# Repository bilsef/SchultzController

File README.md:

# SchultzController

G-code controller for Siemens S (Schultz) feeders

## Arduino based controller in the hardware section.

The controller board distributes power to the feeders and provides the communication interface for 20 feeder units (40 lanes of components).  There are two versions of the controller board.  The KiCad files are in this folder.
* The 4 pin version has 20 individual 4 pin connectors.  One for each feeder unit.
* the 96 pin version has one 96 pin DIN connector compatible with the connector on the Siemens Communication Unit connector board.  This board is Siemens 1710470-Y1032-C1-01-86 and is inside of 00316265S05.
 
## Arduino code in the firmware section.

The board uses a Arduino Nano Every.  This is a low cost arduino which can easily be soldered to the control board.  Edit the config.h file in the arduino sketch to select the type of board you are using, then upload the sketch to the board.

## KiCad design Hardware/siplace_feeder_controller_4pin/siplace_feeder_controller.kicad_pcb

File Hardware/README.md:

# Have the board built by JLCPCB.com

* Go to jlcpcb.com and select SMT Assembly->Quote Now.
* Upload the zip file from the CAM directory of the board you want to build.
* Leave everything as default.  Scroll down to SMT Assembly and click Assemble your PCB boards.
* Choose Assemble bottom side.
* Choose your quantity and click Confirm.
* Upload the BOM and POS xlsx files from the CAM directory.
* Click NEXT.
* Confirm the BOM, click NEXT.
* Confirm the parts placement. If the placement doesn't show up, don't worry about it.  It has been verified.  Click SAVE TO CART and complete your purchase.
* [Buy me a coffee](https://www.buymeacoffee.com/cbVmnqB):coffee::smile:
* After you receive your boards, solder on the Arduino Nano Every using the surface mount pads and castellated holes.  Add connectors of your choice.  The 4 pin layout was made for JST B4B-XH-A(LF)(SN) connectors, but any 2.5mm compatible connector should work.

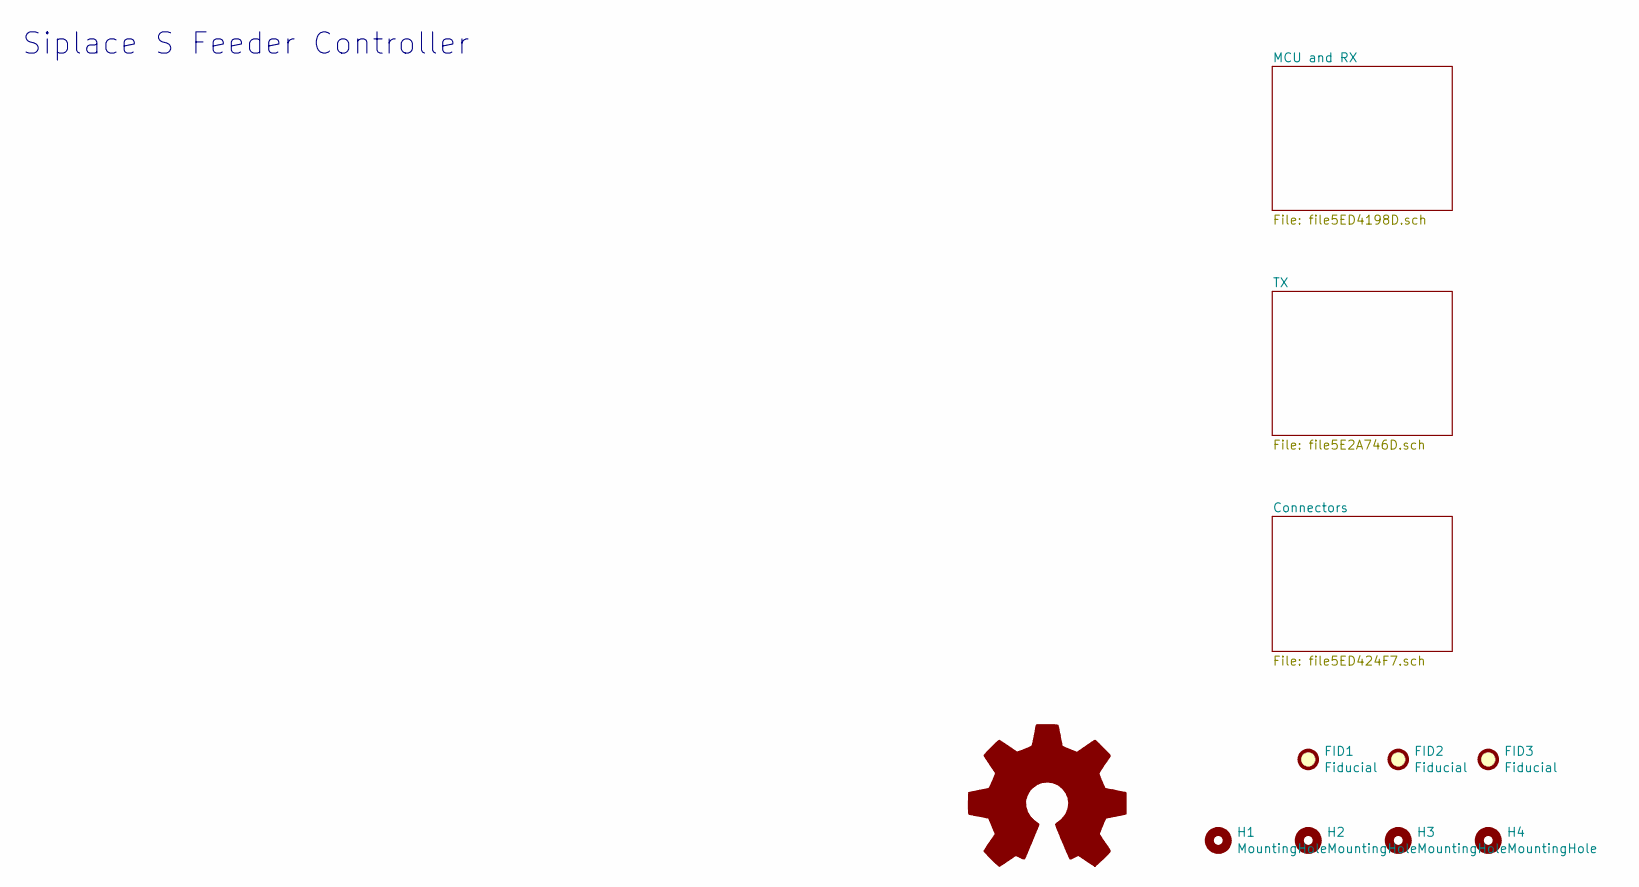
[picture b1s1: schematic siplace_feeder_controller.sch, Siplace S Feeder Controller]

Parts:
FID1, FID2, FID3: Fiducial; Fiducial_1mm_Mask3mm
H1, H2, H3, H4: MountingHole; MountingHole_3.2mm_M3

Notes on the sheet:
Siplace S Feeder Controller

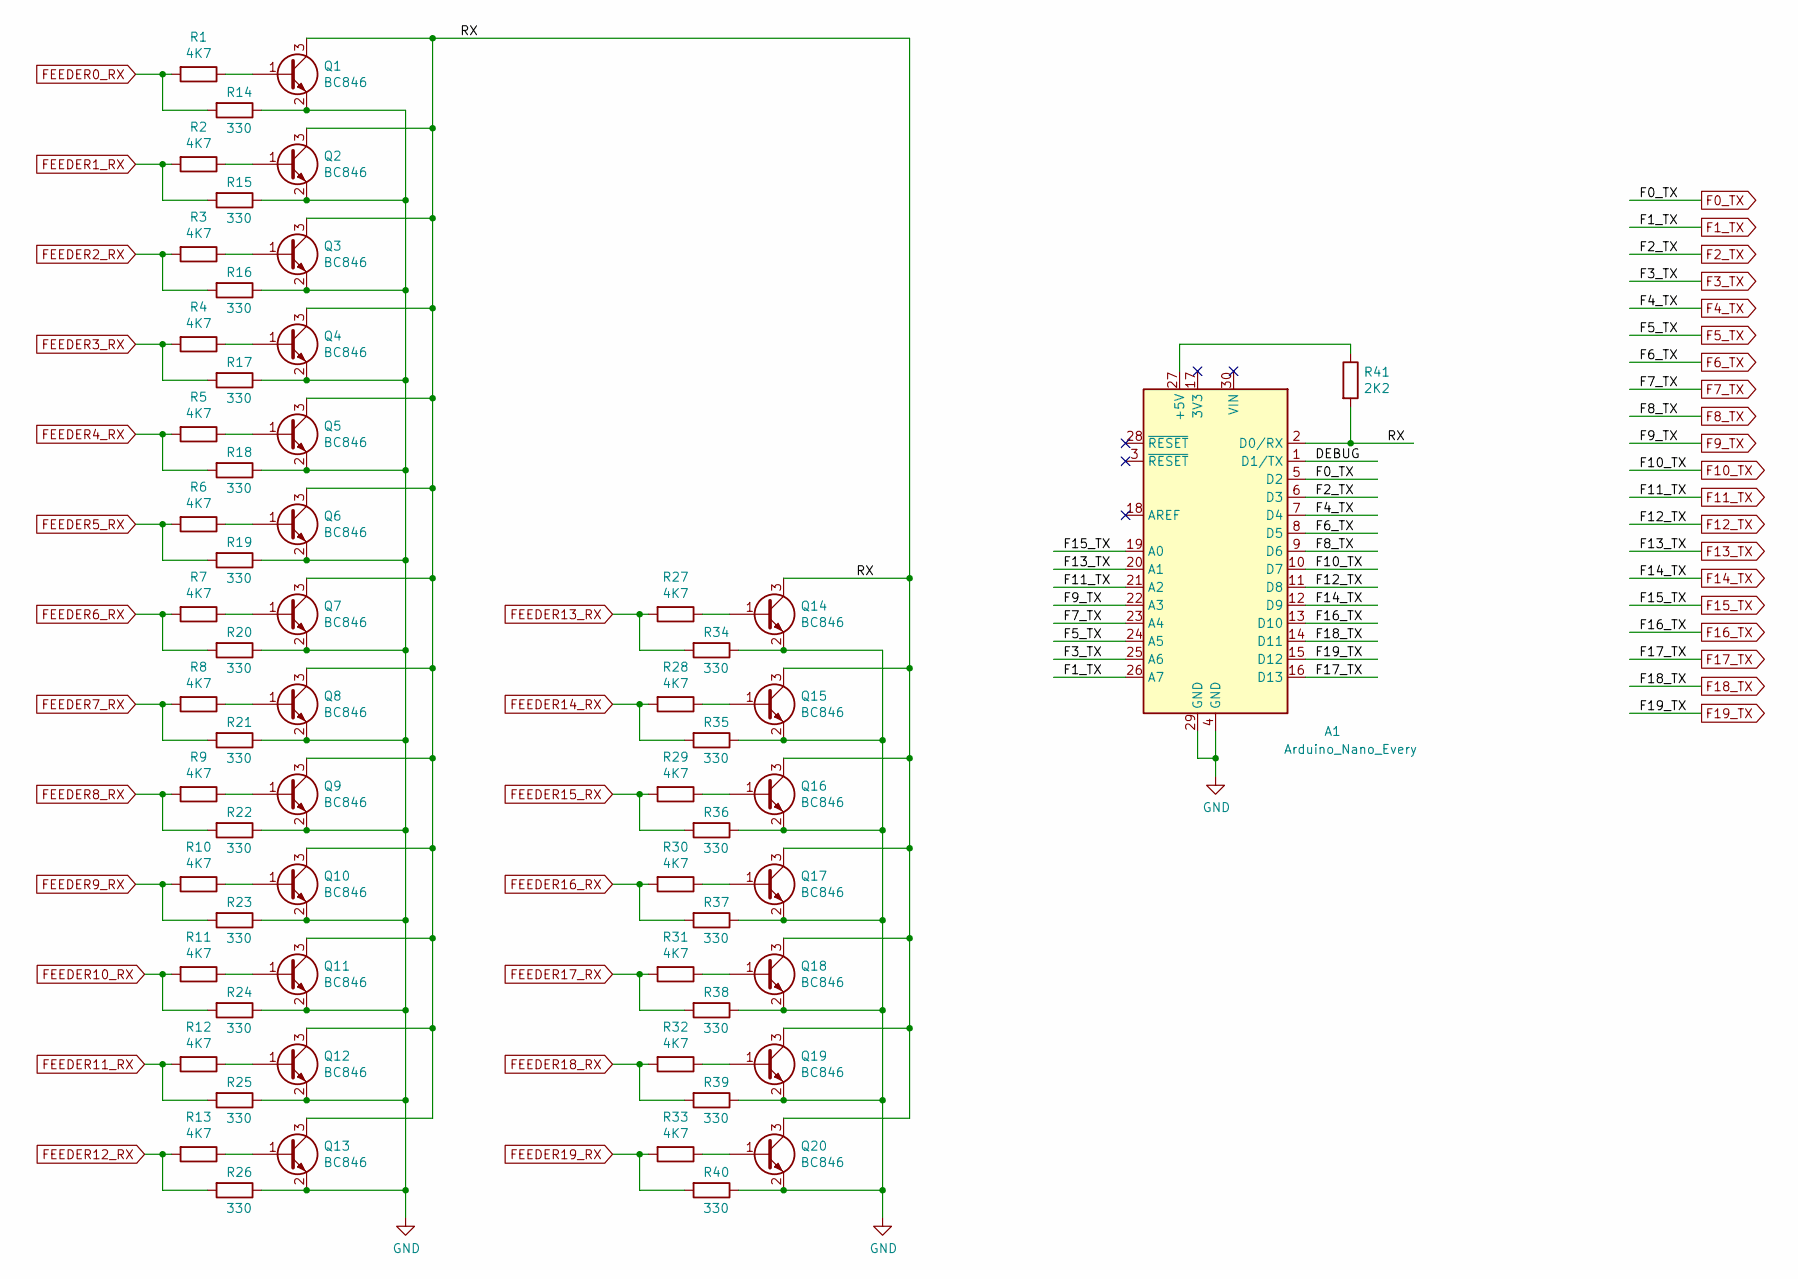
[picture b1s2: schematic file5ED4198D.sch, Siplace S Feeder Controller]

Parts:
A1: Arduino_Nano_Every; NANO_33_Footprint_SMD_Castell
Q1, Q2, Q3, Q4, Q5, Q6, Q7, Q8, Q9, Q10, Q11, Q12, Q13, Q14, Q15, Q16, Q17, Q18, Q19, Q20: BC846; SOT-23
R1, R2, R3, R4, R5, R6, R7, R8, R9, R10, R11, R12, R13, R27, R28, R29, R30, R31, R32, R33: 4K7; R_0603_1608Metric_Pad1.05x0.95mm_HandSolder
R14, R15, R16, R17, R18, R19, R20, R21, R22, R23, R24, R25, R26, R34, R35, R36, R37, R38, R39, R40: 330; R_0603_1608Metric_Pad1.05x0.95mm_HandSolder
R41: 2K2; R_0603_1608Metric_Pad1.05x0.95mm_HandSolder

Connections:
/MCU and RX/DEBUG: A1.1 (D1/TX)
/MCU and RX/RX: A1.2 (D0/RX), Q1.3 (C), Q2.3 (C), Q3.3 (C), Q4.3 (C), Q5.3 (C), Q6.3 (C), Q7.3 (C), Q8.3 (C), Q9.3 (C), Q10.3 (C), Q11.3 (C), Q12.3 (C), Q13.3 (C), Q14.3 (C), Q15.3 (C), Q16.3 (C), Q17.3 (C), Q18.3 (C), Q19.3 (C), Q20.3 (C), R41.2
F0_TX: A1.5 (D2); also elsewhere on the board
F1_TX: A1.26 (A7); also elsewhere on the board
F2_TX: A1.6 (D3); also elsewhere on the board
F3_TX: A1.25 (A6); also elsewhere on the board
F4_TX: A1.7 (D4); also elsewhere on the board
F5_TX: A1.24 (A5); also elsewhere on the board
F6_TX: A1.8 (D5); also elsewhere on the board
F7_TX: A1.23 (A4); also elsewhere on the board
F8_TX: A1.9 (D6); also elsewhere on the board
F9_TX: A1.22 (A3); also elsewhere on the board
F10_TX: A1.10 (D7); also elsewhere on the board
F11_TX: A1.21 (A2); also elsewhere on the board
F12_TX: A1.11 (D8); also elsewhere on the board
F13_TX: A1.20 (A1); also elsewhere on the board
F14_TX: A1.12 (D9); also elsewhere on the board
F15_TX: A1.19 (A0); also elsewhere on the board
F16_TX: A1.13 (D10); also elsewhere on the board
F17_TX: A1.16 (D13); also elsewhere on the board
F18_TX: A1.14 (D11); also elsewhere on the board
F19_TX: A1.15 (D12); also elsewhere on the board
FEEDER0_RX: R1.2, R14.2; also elsewhere on the board
FEEDER1_RX: R2.2, R15.2; also elsewhere on the board
FEEDER2_RX: R3.2, R16.2; also elsewhere on the board
FEEDER3_RX: R4.2, R17.2; also elsewhere on the board
FEEDER4_RX: R5.2, R18.2; also elsewhere on the board
FEEDER5_RX: R6.2, R19.2; also elsewhere on the board
FEEDER6_RX: R7.2, R20.2; also elsewhere on the board
FEEDER7_RX: R8.2, R21.2; also elsewhere on the board
FEEDER8_RX: R9.2, R22.2; also elsewhere on the board
FEEDER9_RX: R10.2, R23.2; also elsewhere on the board
FEEDER10_RX: R11.2, R24.2; also elsewhere on the board
FEEDER11_RX: R12.2, R25.2; also elsewhere on the board
FEEDER12_RX: R13.2, R26.2; also elsewhere on the board
FEEDER13_RX: R27.2, R34.2; also elsewhere on the board
FEEDER14_RX: R28.2, R35.2; also elsewhere on the board
FEEDER15_RX: R29.2, R36.2; also elsewhere on the board
FEEDER16_RX: R30.2, R37.2; also elsewhere on the board
FEEDER17_RX: R31.2, R38.2; also elsewhere on the board
FEEDER18_RX: R32.2, R39.2; also elsewhere on the board
FEEDER19_RX: R33.2, R40.2; also elsewhere on the board
GND: A1.4 (GND), A1.29 (GND), Q1.2 (E), Q2.2 (E), Q3.2 (E), Q4.2 (E), Q5.2 (E), Q6.2 (E), Q7.2 (E), Q8.2 (E), Q9.2 (E), Q10.2 (E), Q11.2 (E), Q12.2 (E), Q13.2 (E), Q14.2 (E), Q15.2 (E), Q16.2 (E), Q17.2 (E), Q18.2 (E), Q19.2 (E), Q20.2 (E), R14.1, R15.1, R16.1, R17.1, R18.1, R19.1, R20.1, R21.1, R22.1, R23.1, R24.1, R25.1, R26.1, R34.1, R35.1, R36.1, R37.1, R38.1, R39.1, R40.1; also elsewhere on the board
unnamed: A1.27 (+5V), R41.1
unnamed: Q1.1 (B), R1.1
unnamed: Q2.1 (B), R2.1
unnamed: Q3.1 (B), R3.1
unnamed: Q4.1 (B), R4.1
unnamed: Q5.1 (B), R5.1
unnamed: Q6.1 (B), R6.1
unnamed: Q7.1 (B), R7.1
unnamed: Q8.1 (B), R8.1
unnamed: Q9.1 (B), R9.1
unnamed: Q10.1 (B), R10.1
unnamed: Q11.1 (B), R11.1
unnamed: Q12.1 (B), R12.1
unnamed: Q13.1 (B), R13.1
unnamed: Q14.1 (B), R27.1
unnamed: Q15.1 (B), R28.1
unnamed: Q16.1 (B), R29.1
unnamed: Q17.1 (B), R30.1
unnamed: Q18.1 (B), R31.1
unnamed: Q19.1 (B), R32.1
unnamed: Q20.1 (B), R33.1

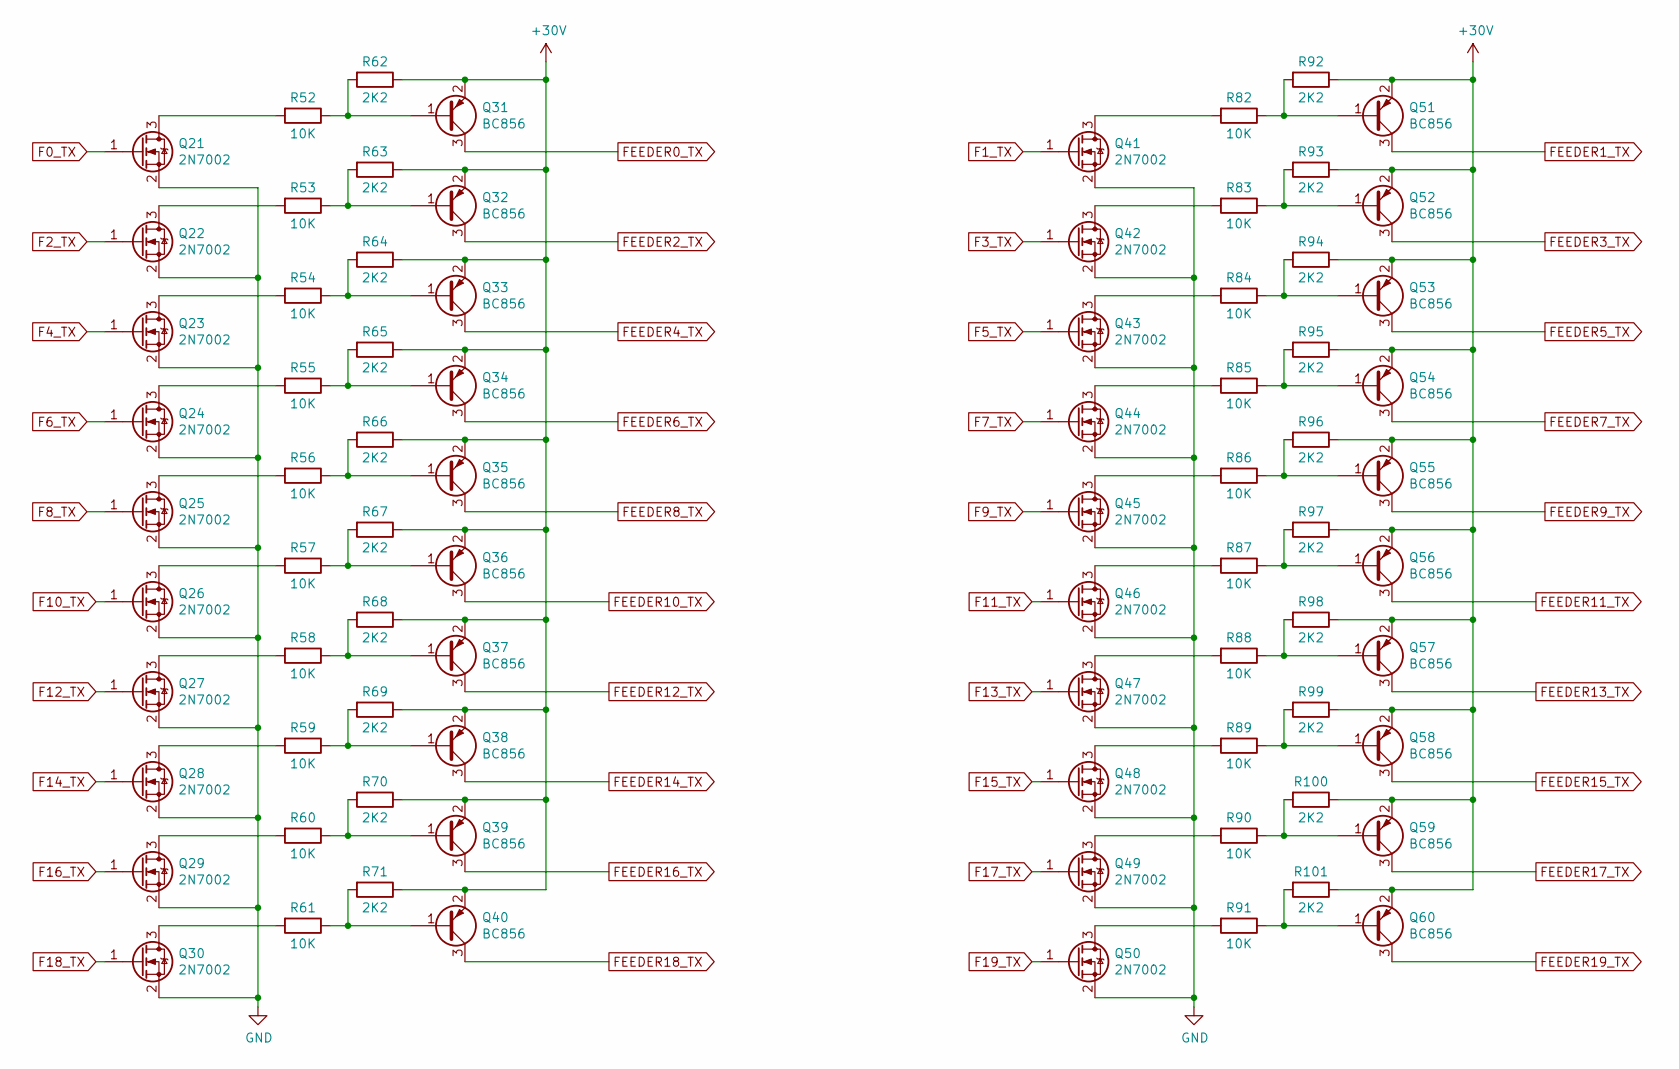
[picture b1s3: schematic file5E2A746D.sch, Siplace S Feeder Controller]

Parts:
Q21, Q22, Q23, Q24, Q25, Q26, Q27, Q28, Q29, Q30, Q41, Q42, Q43, Q44, Q45, Q46, Q47, Q48, Q49, Q50: 2N7002; SOT-23
Q31, Q32, Q33, Q34, Q35, Q36, Q37, Q38, Q39, Q40, Q51, Q52, Q53, Q54, Q55, Q56, Q57, Q58, Q59, Q60: BC856; SOT-23
R52, R53, R54, R55, R56, R57, R58, R59, R60, R61, R82, R83, R84, R85, R86, R87, R88, R89, R90, R91: 10K; R_0603_1608Metric_Pad1.05x0.95mm_HandSolder
R62, R63, R64, R65, R66, R67, R68, R69, R70, R71, R92, R93, R94, R95, R96, R97, R98, R99, R100, R101: 2K2; R_0603_1608Metric_Pad1.05x0.95mm_HandSolder

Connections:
+30V: Q31.2 (E), Q32.2 (E), Q33.2 (E), Q34.2 (E), Q35.2 (E), Q36.2 (E), Q37.2 (E), Q38.2 (E), Q39.2 (E), Q40.2 (E), Q51.2 (E), Q52.2 (E), Q53.2 (E), Q54.2 (E), Q55.2 (E), Q56.2 (E), Q57.2 (E), Q58.2 (E), Q59.2 (E), Q60.2 (E), R62.1, R63.1, R64.1, R65.1, R66.1, R67.1, R68.1, R69.1, R70.1, R71.1, R92.1, R93.1, R94.1, R95.1, R96.1, R97.1, R98.1, R99.1, R100.1, R101.1; also elsewhere on the board
F0_TX: Q21.1 (G); also elsewhere on the board
F1_TX: Q41.1 (G); also elsewhere on the board
F2_TX: Q22.1 (G); also elsewhere on the board
F3_TX: Q42.1 (G); also elsewhere on the board
F4_TX: Q23.1 (G); also elsewhere on the board
F5_TX: Q43.1 (G); also elsewhere on the board
F6_TX: Q24.1 (G); also elsewhere on the board
F7_TX: Q44.1 (G); also elsewhere on the board
F8_TX: Q25.1 (G); also elsewhere on the board
F9_TX: Q45.1 (G); also elsewhere on the board
F10_TX: Q26.1 (G); also elsewhere on the board
F11_TX: Q46.1 (G); also elsewhere on the board
F12_TX: Q27.1 (G); also elsewhere on the board
F13_TX: Q47.1 (G); also elsewhere on the board
F14_TX: Q28.1 (G); also elsewhere on the board
F15_TX: Q48.1 (G); also elsewhere on the board
F16_TX: Q29.1 (G); also elsewhere on the board
F17_TX: Q49.1 (G); also elsewhere on the board
F18_TX: Q30.1 (G); also elsewhere on the board
F19_TX: Q50.1 (G); also elsewhere on the board
FEEDER0_TX: Q31.3 (C); also elsewhere on the board
FEEDER1_TX: Q51.3 (C); also elsewhere on the board
FEEDER2_TX: Q32.3 (C); also elsewhere on the board
FEEDER3_TX: Q52.3 (C); also elsewhere on the board
FEEDER4_TX: Q33.3 (C); also elsewhere on the board
FEEDER5_TX: Q53.3 (C); also elsewhere on the board
FEEDER6_TX: Q34.3 (C); also elsewhere on the board
FEEDER7_TX: Q54.3 (C); also elsewhere on the board
FEEDER8_TX: Q35.3 (C); also elsewhere on the board
FEEDER9_TX: Q55.3 (C); also elsewhere on the board
FEEDER10_TX: Q36.3 (C); also elsewhere on the board
FEEDER11_TX: Q56.3 (C); also elsewhere on the board
FEEDER12_TX: Q37.3 (C); also elsewhere on the board
FEEDER13_TX: Q57.3 (C); also elsewhere on the board
FEEDER14_TX: Q38.3 (C); also elsewhere on the board
FEEDER15_TX: Q58.3 (C); also elsewhere on the board
FEEDER16_TX: Q39.3 (C); also elsewhere on the board
FEEDER17_TX: Q59.3 (C); also elsewhere on the board
FEEDER18_TX: Q40.3 (C); also elsewhere on the board
FEEDER19_TX: Q60.3 (C); also elsewhere on the board
GND: Q21.2 (S), Q22.2 (S), Q23.2 (S), Q24.2 (S), Q25.2 (S), Q26.2 (S), Q27.2 (S), Q28.2 (S), Q29.2 (S), Q30.2 (S), Q41.2 (S), Q42.2 (S), Q43.2 (S), Q44.2 (S), Q45.2 (S), Q46.2 (S), Q47.2 (S), Q48.2 (S), Q49.2 (S), Q50.2 (S); also elsewhere on the board
unnamed: Q21.3 (D), R52.2
unnamed: Q22.3 (D), R53.2
unnamed: Q23.3 (D), R54.2
unnamed: Q24.3 (D), R55.2
unnamed: Q25.3 (D), R56.2
unnamed: Q26.3 (D), R57.2
unnamed: Q27.3 (D), R58.2
unnamed: Q28.3 (D), R59.2
unnamed: Q29.3 (D), R60.2
unnamed: Q30.3 (D), R61.2
unnamed: Q31.1 (B), R52.1, R62.2
unnamed: Q32.1 (B), R53.1, R63.2
unnamed: Q33.1 (B), R54.1, R64.2
unnamed: Q34.1 (B), R55.1, R65.2
unnamed: Q35.1 (B), R56.1, R66.2
unnamed: Q36.1 (B), R57.1, R67.2
unnamed: Q37.1 (B), R58.1, R68.2
unnamed: Q38.1 (B), R59.1, R69.2
unnamed: Q39.1 (B), R60.1, R70.2
unnamed: Q40.1 (B), R61.1, R71.2
unnamed: Q41.3 (D), R82.2
unnamed: Q42.3 (D), R83.2
unnamed: Q43.3 (D), R84.2
unnamed: Q44.3 (D), R85.2
unnamed: Q45.3 (D), R86.2
unnamed: Q46.3 (D), R87.2
unnamed: Q47.3 (D), R88.2
unnamed: Q48.3 (D), R89.2
unnamed: Q49.3 (D), R90.2
unnamed: Q50.3 (D), R91.2
unnamed: Q51.1 (B), R82.1, R92.2
unnamed: Q52.1 (B), R83.1, R93.2
unnamed: Q53.1 (B), R84.1, R94.2
unnamed: Q54.1 (B), R85.1, R95.2
unnamed: Q55.1 (B), R86.1, R96.2
unnamed: Q56.1 (B), R87.1, R97.2
unnamed: Q57.1 (B), R88.1, R98.2
unnamed: Q58.1 (B), R89.1, R99.2
unnamed: Q59.1 (B), R90.1, R100.2
unnamed: Q60.1 (B), R91.1, R101.2

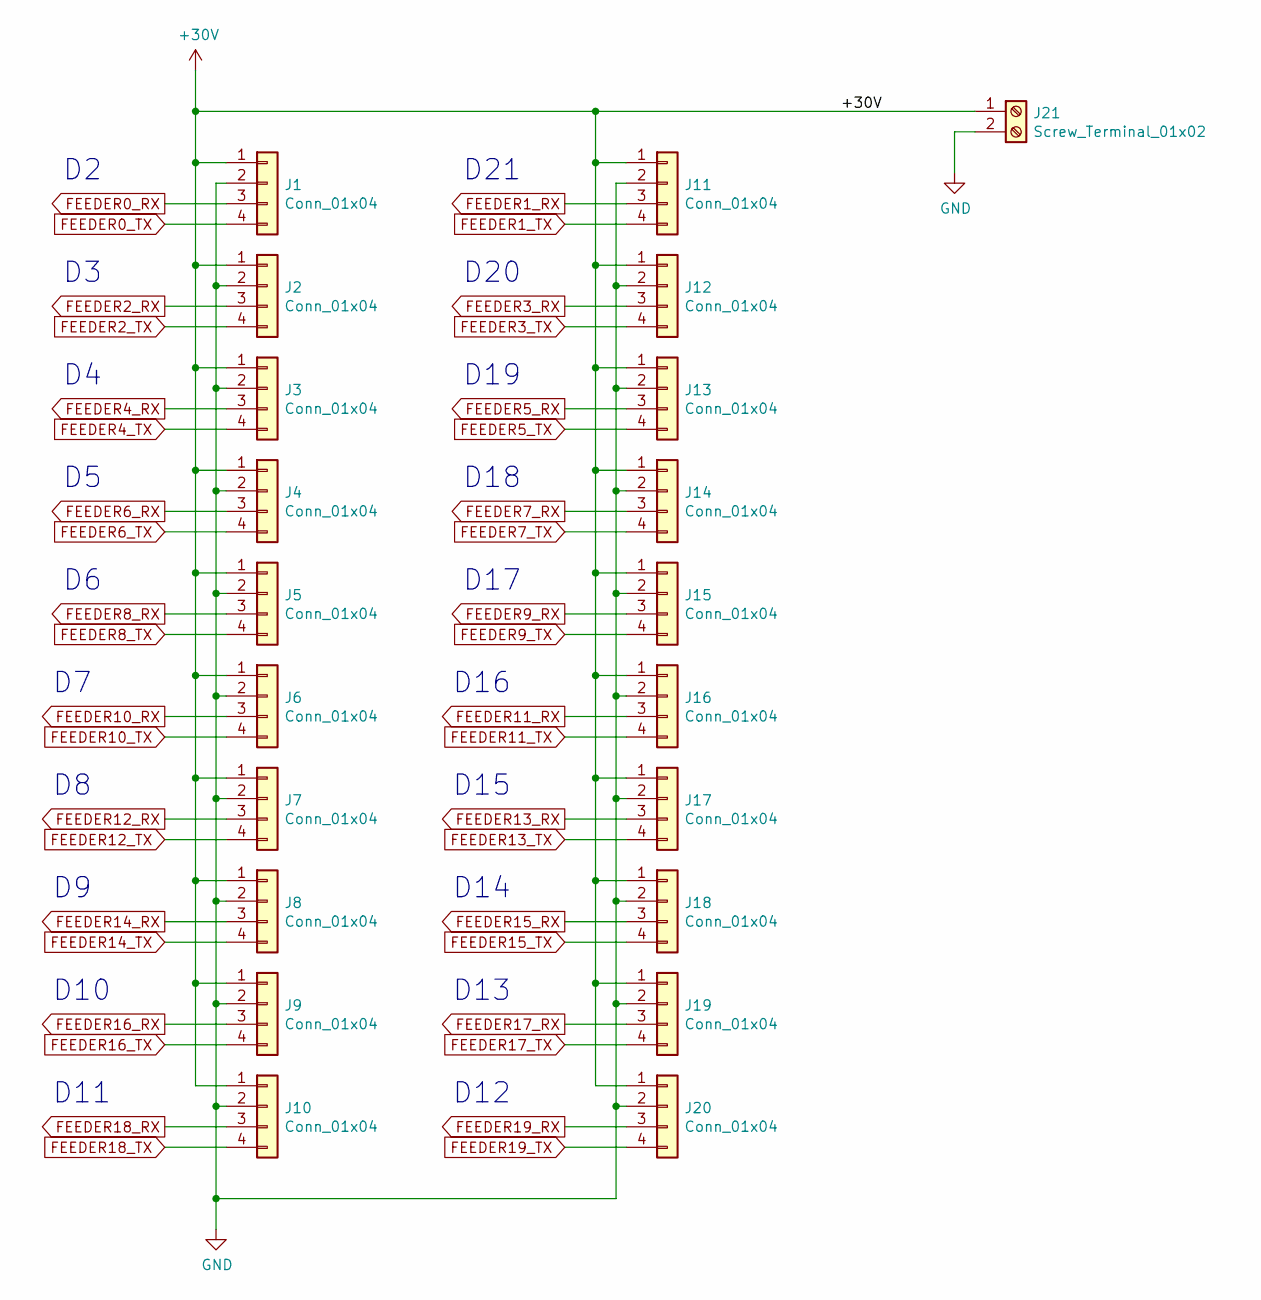
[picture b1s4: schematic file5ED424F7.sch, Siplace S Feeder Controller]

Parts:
J1, J2, J3, J4, J5, J6, J7, J8, J9, J10, J11, J12, J13, J14, J15, J16, J17, J18, J19, J20: Conn_01x04; JST_XH_B4B-XH-A_1x04_P2.50mm_Vertical
J21: Screw_Terminal_01x02; TerminalBlock_Phoenix_MKDS-1,5-2-5.08_1x02_P5.08mm_Horizont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

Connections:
+30V: J1.1, J2.1, J3.1, J4.1, J5.1, J6.1, J7.1, J8.1, J9.1, J10.1, J11.1, J12.1, J13.1, J14.1, J15.1, J16.1, J17.1, J18.1, J19.1, J20.1, J21.1; also elsewhere on the board
FEEDER0_RX: J1.3; also elsewhere on the board
FEEDER0_TX: J1.4; also elsewhere on the board
FEEDER1_RX: J11.3; also elsewhere on the board
FEEDER1_TX: J11.4; also elsewhere on the board
FEEDER2_RX: J2.3; also elsewhere on the board
FEEDER2_TX: J2.4; also elsewhere on the board
FEEDER3_RX: J12.3; also elsewhere on the board
FEEDER3_TX: J12.4; also elsewhere on the board
FEEDER4_RX: J3.3; also elsewhere on the board
FEEDER4_TX: J3.4; also elsewhere on the board
FEEDER5_RX: J13.3; also elsewhere on the board
FEEDER5_TX: J13.4; also elsewhere on the board
FEEDER6_RX: J4.3; also elsewhere on the board
FEEDER6_TX: J4.4; also elsewhere on the board
FEEDER7_RX: J14.3; also elsewhere on the board
FEEDER7_TX: J14.4; also elsewhere on the board
FEEDER8_RX: J5.3; also elsewhere on the board
FEEDER8_TX: J5.4; also elsewhere on the board
FEEDER9_RX: J15.3; also elsewhere on the board
FEEDER9_TX: J15.4; also elsewhere on the board
FEEDER10_RX: J6.3; also elsewhere on the board
FEEDER10_TX: J6.4; also elsewhere on the board
FEEDER11_RX: J16.3; also elsewhere on the board
FEEDER11_TX: J16.4; also elsewhere on the board
FEEDER12_RX: J7.3; also elsewhere on the board
FEEDER12_TX: J7.4; also elsewhere on the board
FEEDER13_RX: J17.3; also elsewhere on the board
FEEDER13_TX: J17.4; also elsewhere on the board
FEEDER14_RX: J8.3; also elsewhere on the board
FEEDER14_TX: J8.4; also elsewhere on the board
FEEDER15_RX: J18.3; also elsewhere on the board
FEEDER15_TX: J18.4; also elsewhere on the board
FEEDER16_RX: J9.3; also elsewhere on the board
FEEDER16_TX: J9.4; also elsewhere on the board
FEEDER17_RX: J19.3; also elsewhere on the board
FEEDER17_TX: J19.4; also elsewhere on the board
FEEDER18_RX: J10.3; also elsewhere on the board
FEEDER18_TX: J10.4; also elsewhere on the board
FEEDER19_RX: J20.3; also elsewhere on the board
FEEDER19_TX: J20.4; also elsewhere on the board
GND: J1.2, J2.2, J3.2, J4.2, J5.2, J6.2, J7.2, J8.2, J9.2, J10.2, J11.2, J12.2, J13.2, J14.2, J15.2, J16.2, J17.2, J18.2, J19.2, J20.2, J21.2; also elsewhere on the board

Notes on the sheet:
D21
D10
D11
D20
D19
D18
D17
D16
D15
D14
D13
D12

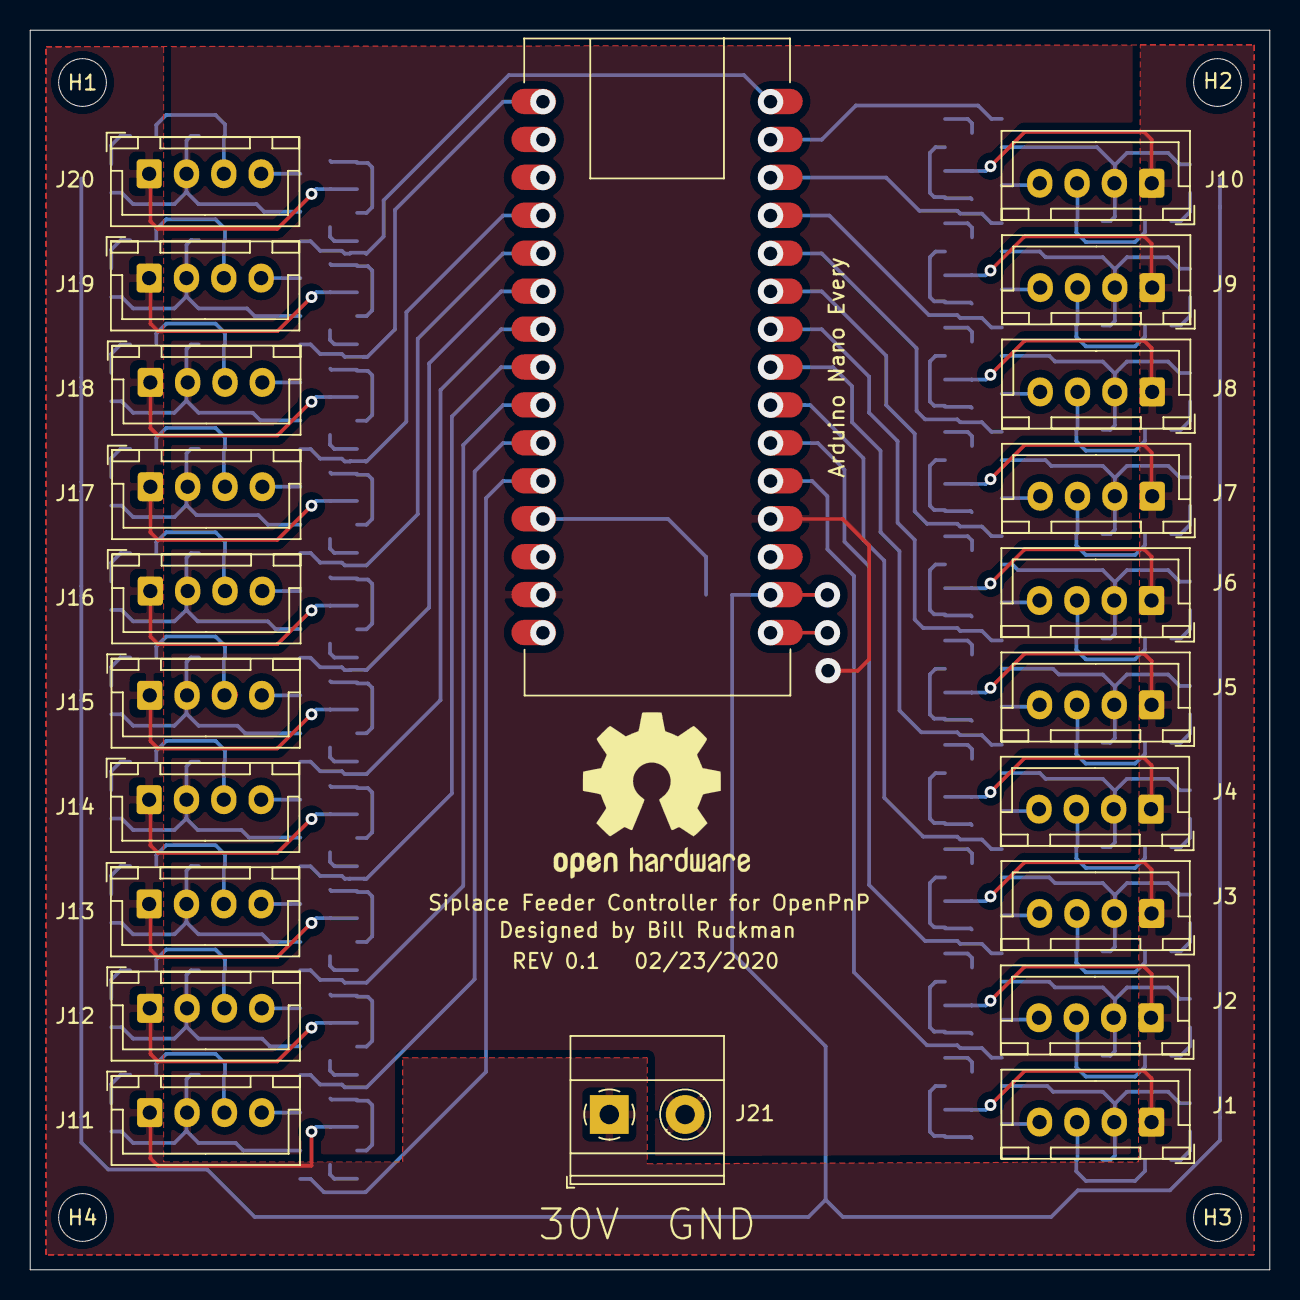
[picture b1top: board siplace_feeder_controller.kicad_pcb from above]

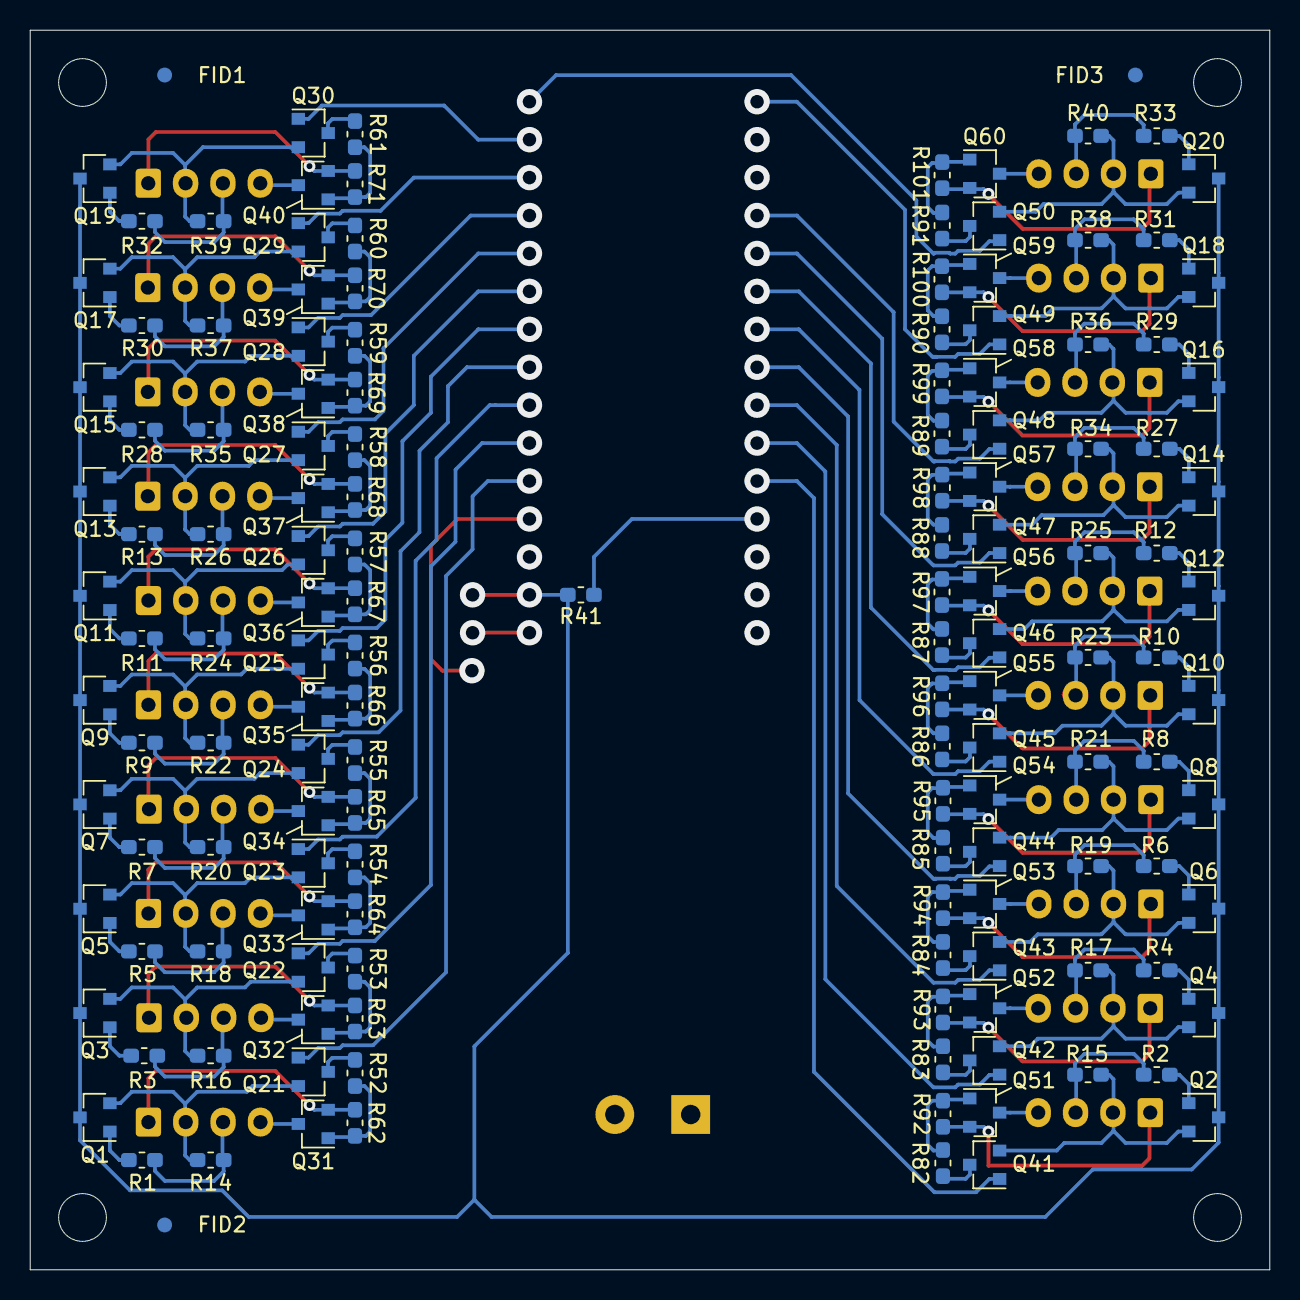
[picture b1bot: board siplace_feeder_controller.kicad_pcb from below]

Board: 2 copper layers, 83.0 x 83.0 mm, 170 parts (144 on the bottom side), 124 nets.

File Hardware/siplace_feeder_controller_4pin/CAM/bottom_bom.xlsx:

Designator | Comment | Footprint | LCSC Part #
Q1 Q2 Q3 Q4 Q5 Q6 Q7 Q8 Q9 Q10 Q11 Q12 Q13 Q14 Q15 Q16 Q17 Q18 Q19 Q20 | BC846 | SOT-23 | C163723
Q21 Q22 Q23 Q24 Q25 Q26 Q27 Q28 Q29 Q30 Q41 Q42 Q43 Q44 Q45 Q46 Q47 Q48 Q49 Q50 | 2N7002 | SOT-23 | C181082
Q60 Q58 Q57 Q56 Q55 Q54 Q53 Q52 Q51 Q31 Q32 Q33 Q34 Q35 Q36 Q37 Q38 Q39 Q40 Q59 | BC856 | SOT-23 | C181145
R1 R2 R3 R4 R5 R6 R7 R8 R9 R10 R11 R12 R13 R27 R28 R29 R30 R31 R32 R33 | 4.7K | R_0603 | C23162
R14 R15 R16 R17 R18 R19 R20 R21 R22 R23 R24 R25 R26 R34 R35 R36 R37 R38 R39 R40 | 330 | R_0603 | C23138
R71 R70 R69 R68 R67 R66 R65 R64 R63 R62 R101 R92 R93 R94 R95 R96 R97 R98 R99 R1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 | 1.2K | R_0603 | C22765
R83 R84 R85 R86 R87 R88 R89 R91 R61 R60 R59 R58 R57 R56 R55 R54 R53 R52 R90 R82 | 10K | R_0603 | C25804
R41 | 2.2K | R_0603 | C4190

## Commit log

2020-02-23 Update
    Add new gcodes and rearrange numbers.
    Change port numbers for 96 pin connector version.
2020-03-02 Add ability to set pitch from GUI
2020-03-08 Fix bug where setting pitch was corrupting EEPROM
    Fix bug where setting pitch was corrupting EEPROM.
    Add command to set ID and initialize EEPROM.
2020-03-13 Added hardware files
2020-03-13 Update CAM files
2020-03-13 rename
2020-03-13 remove extraneous files
2020-03-13 add CAM zip file
2020-03-13 file clean-up
2020-03-13 add readme
2020-03-15 Add scripts
    OpenPnP scripts to help with creating and using feeders.
2020-03-18 Fix compiler warnings
2021-06-04 Removed F() macro calls
    Latest IDE failed to compile for Nano Every
2021-06-06 Modify M115 response
2021-06-06 Fix formatting of M115 message
2021-06-07 Improve command buffering
    Allow a new command to come in while processing another one.
2021-06-07 Fix typo
2021-06-07 remove debug code
2021-06-13 Update AlignFeeders.js
    Skip slots that do not have a feeder loaded.
